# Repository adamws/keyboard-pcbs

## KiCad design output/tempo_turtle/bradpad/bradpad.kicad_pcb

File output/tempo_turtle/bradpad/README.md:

## tempo_turtle/bradpad

[layout](bradpad-kle.json) - [PCB](bradpad.kicad_pcb)

{:loading="lazy"}

[Open in keyboard-layout-editor](http://www.keyboard-layout-editor.com/##@@=0,0&=0,1&=0,2&=0,3;&@=1,0&=1,1&=1,2&=1,3;&@=2,0&=2,1&=2,2&=2,3;&@=3,0&=3,1&=3,2&=3,3;&@_w:2;&=4,1&_w:2;&=4,2)

{:loading="lazy"}

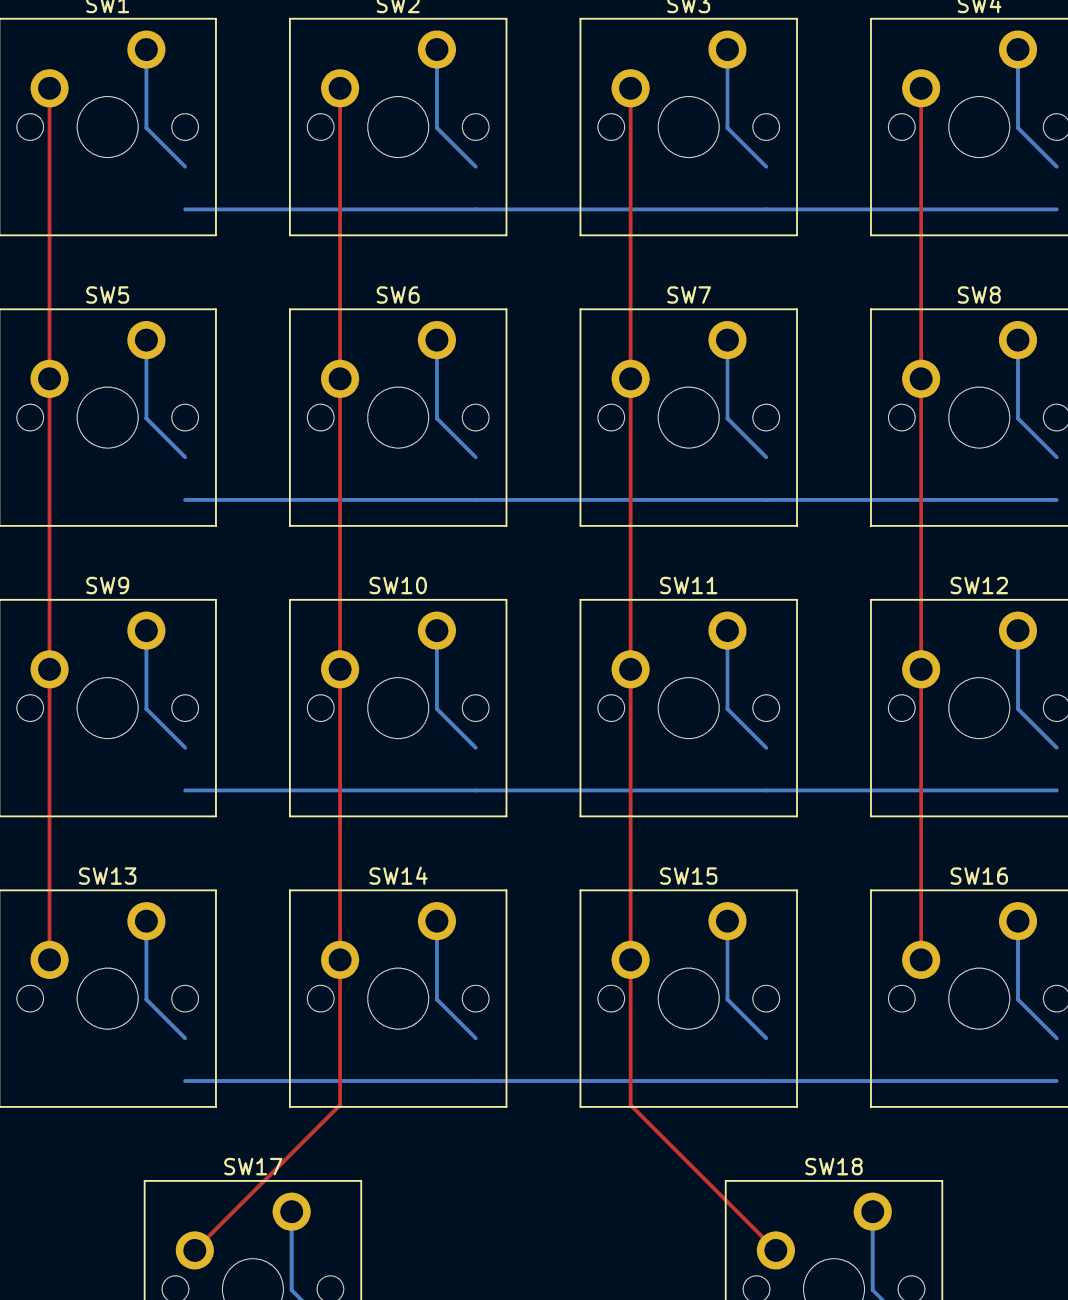
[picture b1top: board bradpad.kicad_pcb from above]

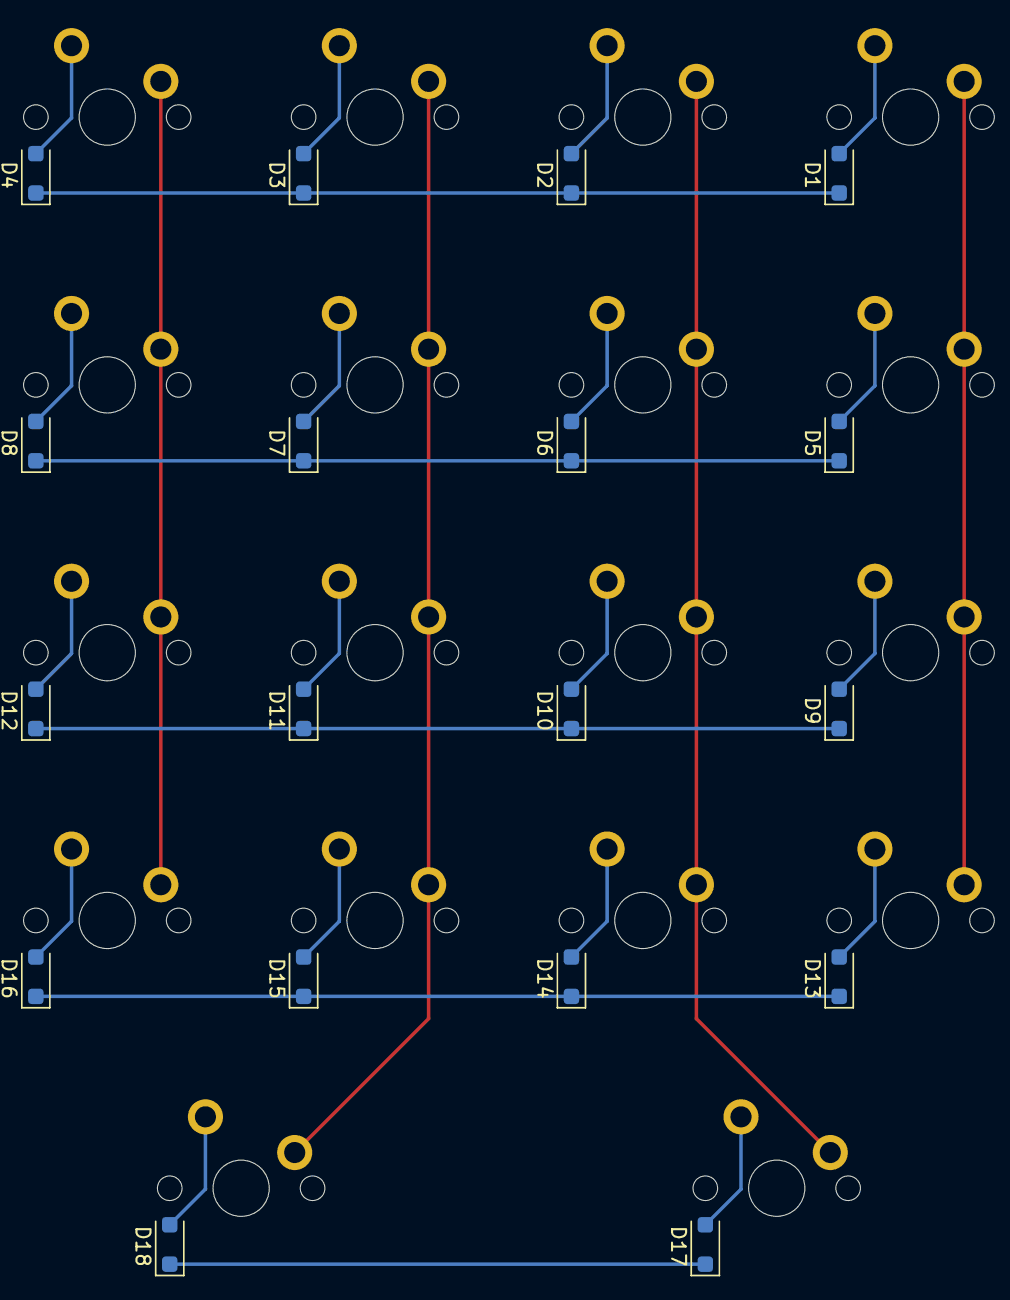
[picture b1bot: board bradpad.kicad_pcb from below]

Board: 2 copper layers, 36 parts (18 on the bottom side), 27 nets.

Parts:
D1, D2, D3, D4, D5, D6, D7, D8, D9, D10, D11, D12, D13, D14, D15, D16, D17, D18: D_SOD-123F
SW1, SW2, SW3, SW4, SW5, SW6, SW7, SW8, SW9, SW10, SW11, SW12, SW13, SW14, SW15, SW16, SW17, SW18: SW_Cherry_MX_PCB_1.00u

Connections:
COL0: SW1.1, SW5.1, SW9.1, SW13.1
COL1: SW2.1, SW6.1, SW10.1, SW14.1, SW17.1
COL2: SW3.1, SW7.1, SW11.1, SW15.1, SW18.1
COL3: SW4.1, SW8.1, SW12.1, SW16.1
unnamed: D1.2, SW1.2
unnamed: D2.2, SW2.2
unnamed: D3.2, SW3.2
unnamed: D4.2, SW4.2
unnamed: D5.2, SW5.2
unnamed: D6.2, SW6.2
unnamed: D7.2, SW7.2
unnamed: D8.2, SW8.2
unnamed: D9.2, SW9.2
unnamed: D10.2, SW10.2
unnamed: D11.2, SW11.2
unnamed: D12.2, SW12.2
unnamed: D13.2, SW13.2
unnamed: D14.2, SW14.2
unnamed: D15.2, SW15.2
unnamed: D16.2, SW16.2
unnamed: D17.2, SW17.2
unnamed: D18.2, SW18.2
ROW0: D1.1, D2.1, D3.1, D4.1
ROW1: D5.1, D6.1, D7.1, D8.1
ROW2: D9.1, D10.1, D11.1, D12.1
ROW3: D13.1, D14.1, D15.1, D16.1
ROW4: D17.1, D18.1

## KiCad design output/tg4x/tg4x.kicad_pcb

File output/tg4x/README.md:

## tg4x/tg4x

[layout](tg4x-kle.json) - [PCB](tg4x.kicad_pcb)

{:loading="lazy"}

[Open in keyboard-layout-editor](http://www.keyboard-layout-editor.com/##@@_c=#aaaaaa;&=0,0&_c=#cccccc;&=0,1&=0,2&=0,3&=0,4&=0,5&=0,6&=4,0&=4,1&=4,2&=4,3&=4,4&_c=#aaaaaa;&=4,5;&@_w:1.25;&=1,0&_c=#cccccc;&=1,1&=1,2&=1,3&=1,4&=1,5&=1,6&=5,0&=5,1&=5,2&=5,3&_c=#aaaaaa&w:1.75;&=5,4;&@_w:1.75;&=2,0&_c=#cccccc;&=2,1&=2,2&=2,3&=2,4&=2,5&=2,6&=6,0&=6,1&=6,2&=6,3&_c=#aaaaaa&w:1.25;&=6,4;&@_w:1.25;&=3,0&_w:1.25;&=3,1&_w:1.25;&=3,2&_c=#cccccc&w:2.25;&=3,4&_w:2.75;&=3,5&_c=#aaaaaa&w:1.25;&=7,1&=7,2&=7,3&=7,4)

{:loading="lazy"}

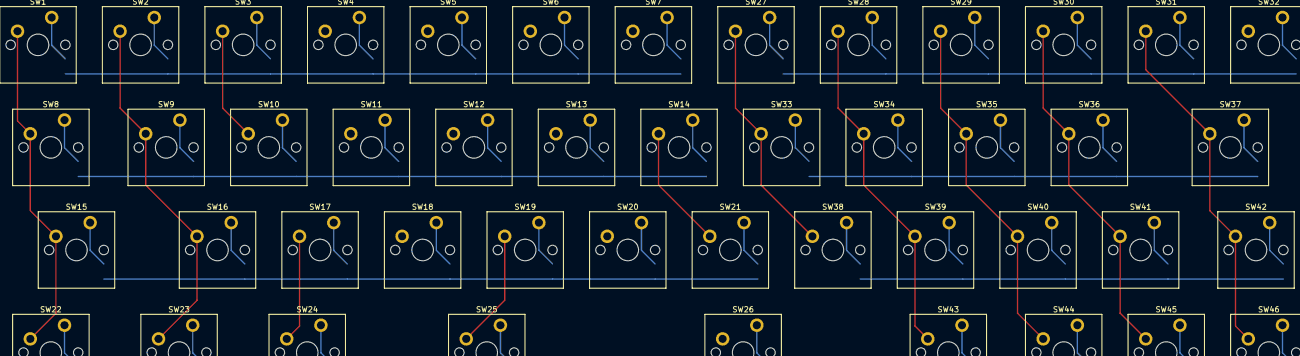
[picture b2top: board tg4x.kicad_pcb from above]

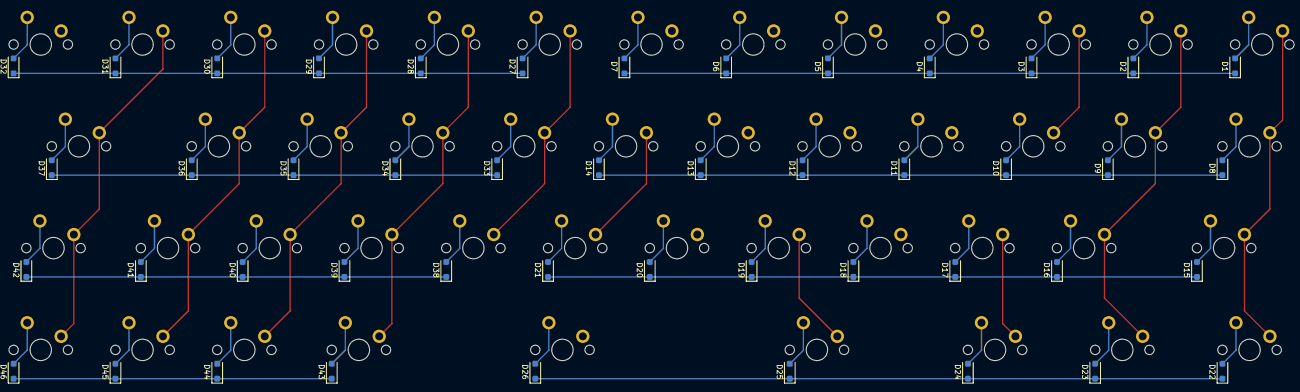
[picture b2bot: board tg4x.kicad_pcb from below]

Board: 2 copper layers, 92 parts (46 on the bottom side), 61 nets.

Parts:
D1, D2, D3, D4, D5, D6, D7, D8, D9, D10, D11, D12, D13, D14, D15, D16, D17, D18, D19, D20, D21, D22, D23, D24, D25, D26, D27, D28, D29, D30, D31, D32, D33, D34, D35, D36, D37, D38, D39, D40, D41, D42, D43, D44, D45, D46: D_SOD-123F
SW1, SW2, SW3, SW4, SW5, SW6, SW7, SW8, SW9, SW10, SW11, SW12, SW13, SW14, SW15, SW16, SW17, SW18, SW19, SW20, SW21, SW22, SW23, SW24, SW25, SW26, SW27, SW28, SW29, SW30, SW31, SW32, SW33, SW34, SW35, SW36, SW37, SW38, SW39, SW40, SW41, SW42, SW43, SW44, SW45, SW46: SW_Cherry_MX_PCB_1.00u

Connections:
COL0: SW1.1, SW8.1, SW15.1, SW22.1, SW27.1, SW33.1, SW38.1
COL1: SW2.1, SW9.1, SW16.1, SW23.1, SW28.1, SW34.1, SW39.1, SW43.1
COL2: SW3.1, SW10.1, SW17.1, SW24.1, SW29.1, SW35.1, SW40.1, SW44.1
COL3: SW4.1, SW11.1, SW18.1, SW30.1, SW36.1, SW41.1, SW45.1
COL4: SW5.1, SW12.1, SW19.1, SW25.1, SW31.1, SW37.1, SW42.1, SW46.1
COL5: SW6.1, SW13.1, SW20.1, SW26.1, SW32.1
COL6: SW7.1, SW14.1, SW21.1
unnamed: D1.2, SW1.2
unnamed: D2.2, SW2.2
unnamed: D3.2, SW3.2
unnamed: D4.2, SW4.2
unnamed: D5.2, SW5.2
unnamed: D6.2, SW6.2
unnamed: D7.2, SW7.2
unnamed: D8.2, SW8.2
unnamed: D9.2, SW9.2
unnamed: D10.2, SW10.2
unnamed: D11.2, SW11.2
unnamed: D12.2, SW12.2
unnamed: D13.2, SW13.2
unnamed: D14.2, SW14.2
unnamed: D15.2, SW15.2
unnamed: D16.2, SW16.2
unnamed: D17.2, SW17.2
unnamed: D18.2, SW18.2
unnamed: D19.2, SW19.2
unnamed: D20.2, SW20.2
unnamed: D21.2, SW21.2
unnamed: D22.2, SW22.2
unnamed: D23.2, SW23.2
unnamed: D24.2, SW24.2
unnamed: D25.2, SW25.2
unnamed: D26.2, SW26.2
unnamed: D27.2, SW27.2
unnamed: D28.2, SW28.2
unnamed: D29.2, SW29.2
unnamed: D30.2, SW30.2
unnamed: D31.2, SW31.2
unnamed: D32.2, SW32.2
unnamed: D33.2, SW33.2
unnamed: D34.2, SW34.2
unnamed: D35.2, SW35.2
unnamed: D36.2, SW36.2
unnamed: D37.2, SW37.2
unnamed: D38.2, SW38.2
unnamed: D39.2, SW39.2
unnamed: D40.2, SW40.2
unnamed: D41.2, SW41.2
unnamed: D42.2, SW42.2
unnamed: D43.2, SW43.2
unnamed: D44.2, SW44.2
unnamed: D45.2, SW45.2
unnamed: D46.2, SW46.2
ROW0: D1.1, D2.1, D3.1, D4.1, D5.1, D6.1, D7.1
ROW1: D8.1, D9.1, D10.1, D11.1, D12.1, D13.1, D14.1
ROW2: D15.1, D16.1, D17.1, D18.1, D19.1, D20.1, D21.1
ROW3: D22.1, D23.1, D24.1, D25.1, D26.1
ROW4: D27.1, D28.1, D29.1, D30.1, D31.1, D32.1
ROW5: D33.1, D34.1, D35.1, D36.1, D37.1
ROW6: D38.1, D39.1, D40.1, D41.1, D42.1
ROW7: D43.1, D44.1, D45.1, D46.1
